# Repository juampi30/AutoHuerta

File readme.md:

# 🌱 AutoHuerta – Sistema Automatizado de Hidroponía Indoor

**AutoHuerta** es un sistema de cultivo hidropónico de interior (*indoor*) diseñado para germinar y desarrollar plantas sin necesidad de suelo agrícola ni luz solar directa. El equipo automatiza los ciclos de iluminación, ventilación y recirculación de nutrientes mediante un microcontrolador **STM32**, permitiendo el cultivo doméstico limpio y autónomo durante todo el año.

Desarrollado por el grupo **HidroTec** (Juan Pablo de Urquiza y Gianluca Mariotto) para la materia *Proyecto y Diseño Electrónico* — E.E.S.T. N° 5 "2 de Abril", Temperley.

---

## ⚙️ Características Principales

* **Iluminación Full Spectrum:** Módulo LED COB Full Spectrum de 50 W (rango PAR 400–700 nm) con fotoperíodo automático de **18 h de luz / 6 h de oscuridad**.
* **Recirculación y Oxigenación Hídrica:** Bomba sumergible de 5 VCC activada **5 minutos por hora** para mantener oxigenada la solución nutritiva y evitar el estancamiento.
* **Control Térmico Sincronizado:** Disipador de aluminio con ventilador axial de 12 VCC accionado junto con la luminaria COB (con soporte para control de velocidad por PWM).
* **Electrónica Protegida y Escalable:** PCB doble faz con etapas de potencia optoacopladas (`PC817`), reguladores independientes (`L7805`) para lógica y motor, y pinera de expansión de 10 pines (7 GPIO + GND + 5 V + 12 V) para futuros sensores o conectividad IoT.

---

## 📂 Estructura del Repositorio

El proyecto está organizado en las siguientes carpetas para facilitar su reproducción:

```text
AutoHuerta/
├── Diseño 3D/      # Planos y modelos 3D del gabinete, soportes de disipador y canastas hidropónicas
├── Hardware/       # Proyecto en KiCad (esquemáticos, diseño de PCB doble faz, render 3D y lista de componentes)
├── Software/       # Código fuente en C/C++ (.ino) para el microcontrolador STM32F103C8T6
└── README.md       # Documentación general del proyecto
```

---

## 🛠️ Requisitos de Hardware y Software

* **Microcontrolador:** STM32F103C8T6 (*Blue Pill*, ARM Cortex-M3).
* **Programador:** ST-Link V2.
* **Entorno de desarrollo:** Arduino IDE con el núcleo **STM32duino** instalado.
* **CAD Electrónico:** KiCad (para abrir los archivos de la carpeta `/Hardware`).

---

## 🚀 Puesta en Marcha Rápida

1. **Preparar la solución nutritiva:** Llenar el recipiente del cajón frontal con agua limpia y agregar dos tapas de nutrientes *macro* y dos tapas de nutrientes *micro*.
2. **Colocar los cultivos:** Ubicar las plántulas en las canastas perforadas asegurando que sus raíces queden en contacto con el agua.
3. **Encender:** Conectar el equipo a la red eléctrica de **220 VCA**. El sistema iniciará automáticamente los ciclos de luz, ventilación y bombeo sin requerir configuración adicional.
4. **Mantenimiento:** Renovar el agua con nutrientes aproximadamente cada **25 días**.

---

## 📄 Licencia y Créditos

Proyecto educativo y de código abierto desarrollado por **HidroTec** — E.E.S.T. N° 5 "2 de Abril" (Temperley, Buenos Aires, Argentina).

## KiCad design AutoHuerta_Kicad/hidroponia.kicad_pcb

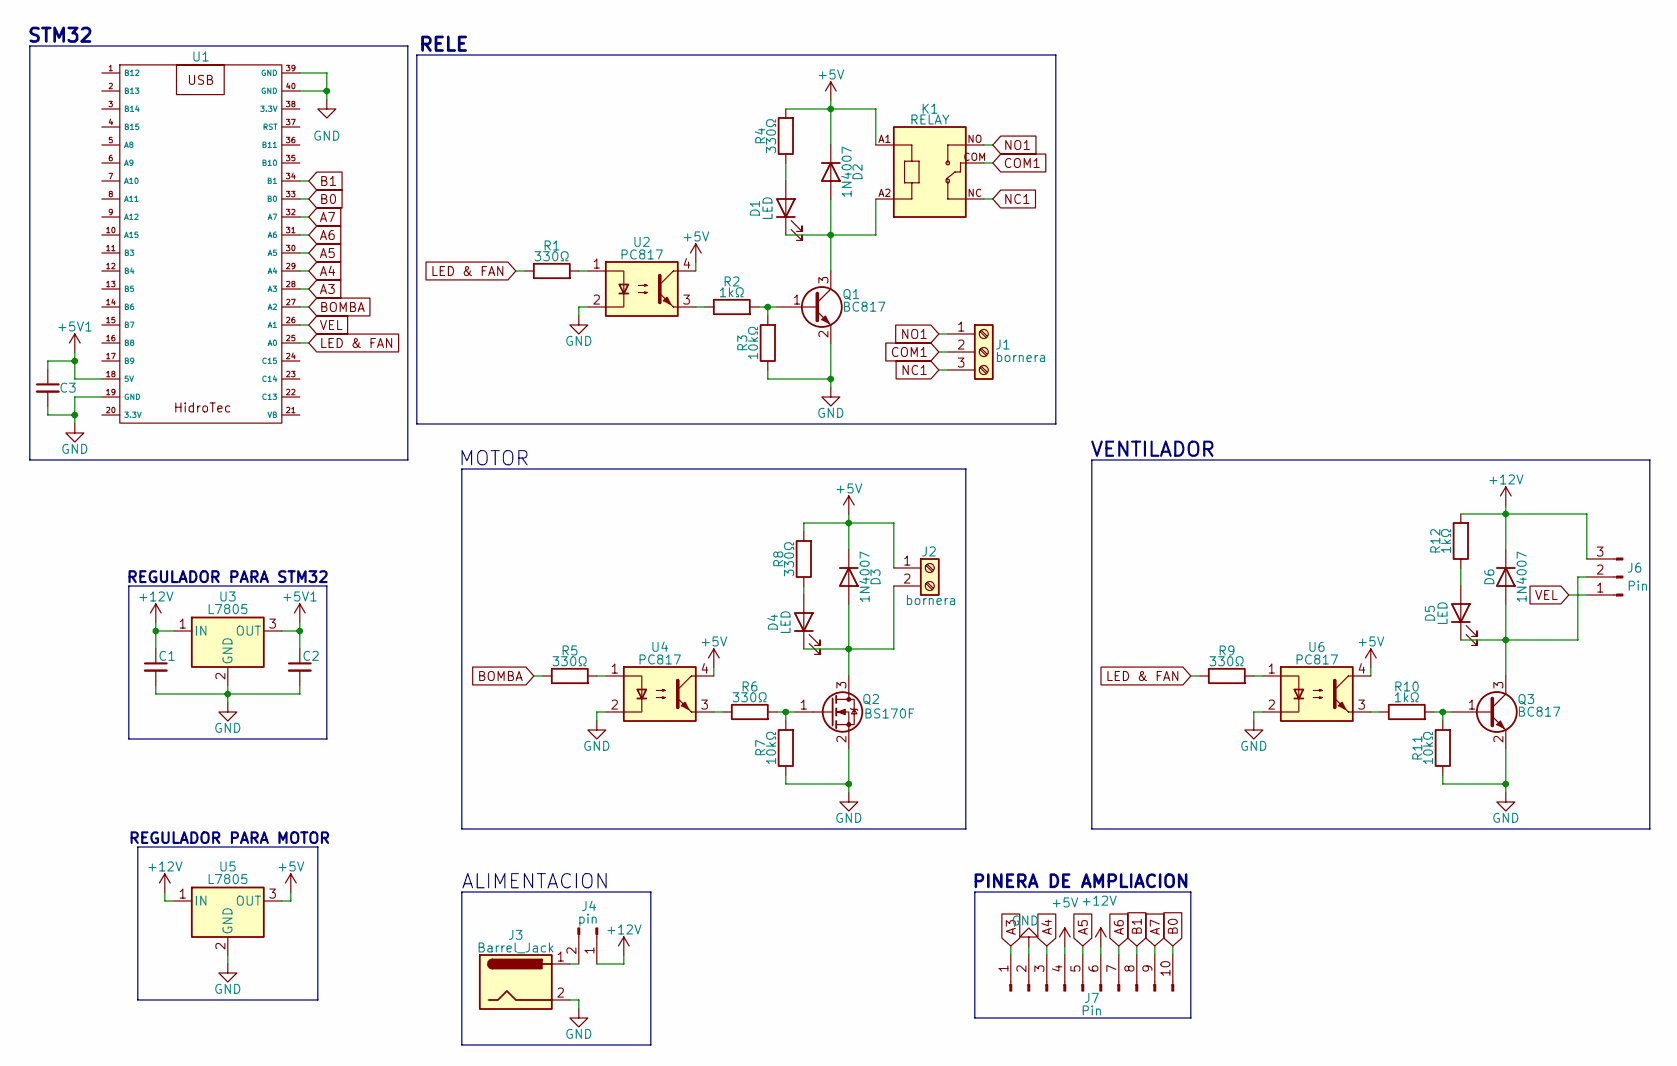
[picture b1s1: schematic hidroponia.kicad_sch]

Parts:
C1: 0,33uf; C_0805_2012Metric_Pad1.18x1.45mm_HandSolder
C2, C3: 0,1uf; C_0805_2012Metric_Pad1.18x1.45mm_HandSolder
D1, D4, D5: LED; LED_D3.0mm
D2, D3, D6: 1N4007; D_SMA
J1: bornera; TerminalBlock_bornier-3_P5.08mm
J2: bornera; TerminalBlock_MetzConnect_Type011_RT05502HBWC_1x02_P5.00mm_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
J3: Barrel_Jack; BarrelJack_GCT_DCJ200-10-A_Horizontal
J4: pin; PinHeader_1x02_P2.54mm_Vertical
J6: Pin; Molex_KK-254_AE-6410-03A_1x03_P2.54mm_Vertical
J7: Pin; IDC-Header_2x05-1MP_P2.54mm_Latch6.5mm_Vertical
K1: RELAY; RELAY_SRD-05VDC-SL-C
Q1, Q3: BC817; SOT-23
Q2: BS170F; SOT-23
R1, R4, R5, R6, R8, R9: 330Ω; R_0805_2012Metric
R2, R10, R12: 1kΩ; R_0805_2012Metric
R3, R7, R11: 10kΩ; R_0805_2012Metric
U1: stm32
U2, U4, U6: PC817; DIP-4_W7.62mm_LongPads
U3, U5: L7805; TO-252-2

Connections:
+5V: D2.1 (K), D3.1 (K), J2.1, J7.4, K1.A1, R4.2, R8.2, U2.4, U4.4, U5.3 (OUT), U6.4
+5V1: C2.1, C3.1, U1.18 (5V), U3.3 (OUT)
+12V: C1.1, D6.1 (K), J4.1, J6.3, J7.6, R12.2, U3.1 (IN), U5.1 (IN)
A3: J7.1, U1.28 (A3)
A4: J7.3, U1.29 (A4)
A5: J7.5, U1.30 (A5)
A6: J7.7, U1.31 (A6)
A7: J7.9, U1.32 (A7)
B0: J7.10, U1.33 (B0)
B1: J7.8, U1.34 (B1)
BOMBA: R5.1, U1.27 (A2)
COM1: J1.2, K1.COM
GND: C1.2, C2.2, C3.2, J3.2, J7.2, Q1.2 (E), Q2.2 (S), Q3.2 (E), R3.1, R7.1, R11.1, U1.19 (GND), U1.39 (GND), U1.40 (GND), U2.2, U3.2 (GND), U4.2, U5.2 (GND), U6.2
LED & FAN: R1.1, R9.1, U1.25 (A0)
NC1: J1.3, K1.NC
NO1: J1.1, K1.NO
unnamed: D1.2 (A), R4.1
unnamed: D1.1 (K), D2.2 (A), K1.A2, Q1.3 (C)
unnamed: D3.2 (A), D4.1 (K), J2.2, Q2.3 (D)
unnamed: D4.2 (A), R8.1
unnamed: D5.2 (A), R12.1
unnamed: D5.1 (K), D6.2 (A), J6.2, Q3.3 (C)
unnamed: J3.1, J4.2
unnamed: Q1.1 (B), R2.2, R3.2
unnamed: Q2.1 (G), R6.2, R7.2
unnamed: Q3.1 (B), R10.2, R11.2
unnamed: R1.2, U2.1
unnamed: R2.1, U2.3
unnamed: R5.2, U4.1
unnamed: R6.1, U4.3
unnamed: R9.2, U6.1
unnamed: R10.1, U6.3
VEL: J6.1, U1.26 (A1)

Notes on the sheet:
RELE
REGULADOR PARA STM32
STM32
REGULADOR PARA MOTOR
ALIMENTACION
VENTILADOR
PINERA DE AMPLIACION
MOTOR

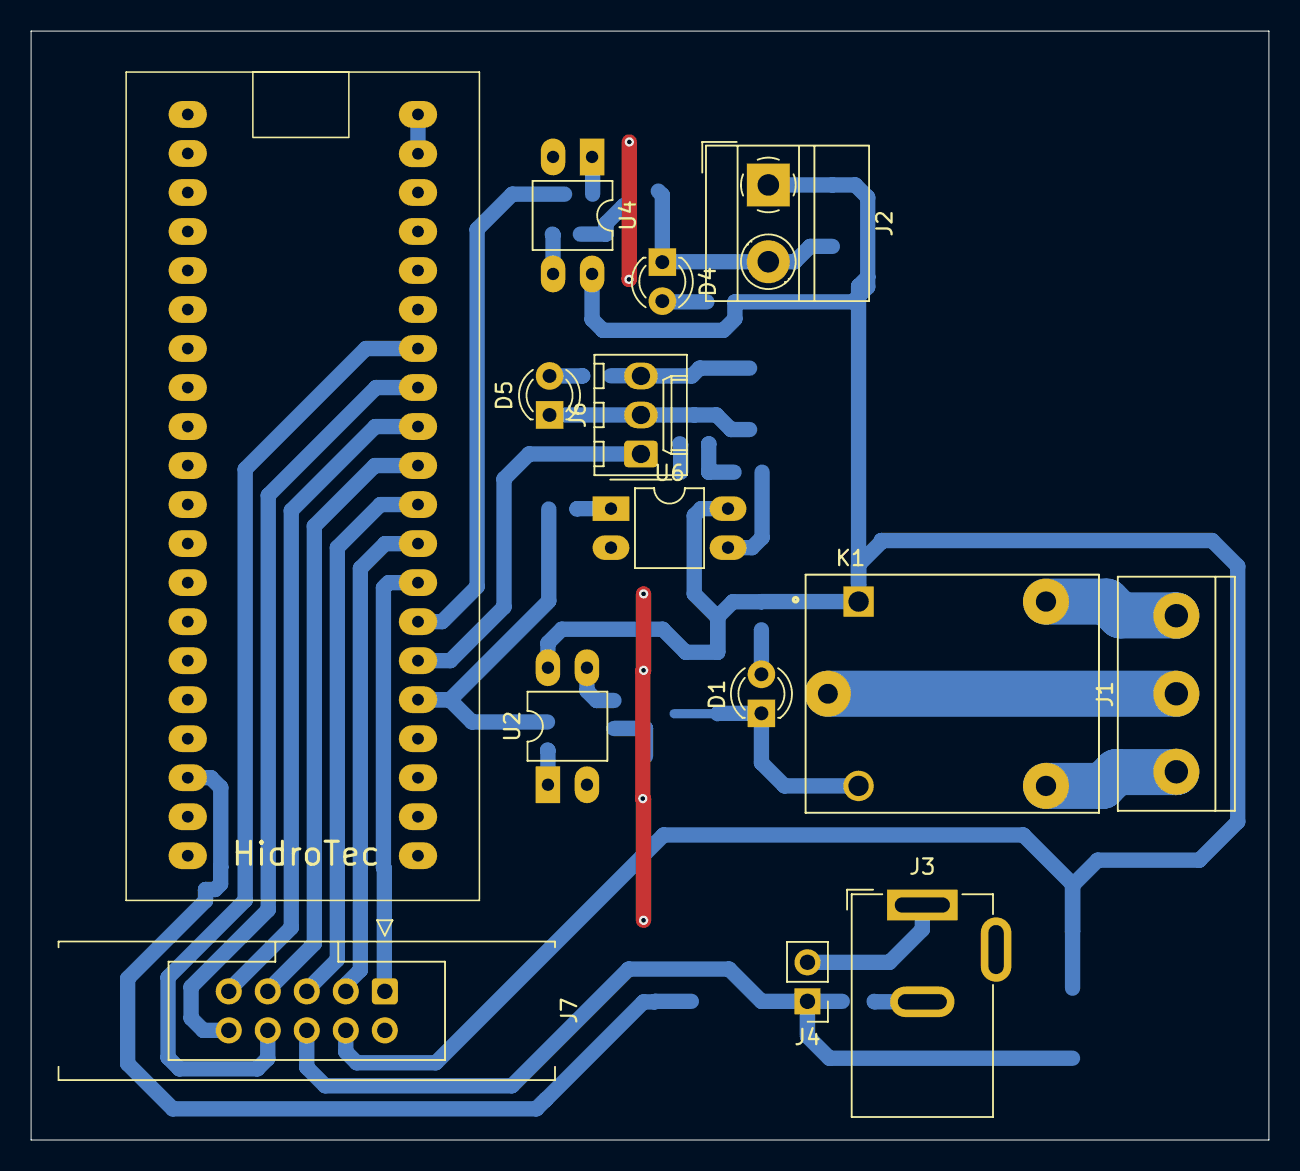
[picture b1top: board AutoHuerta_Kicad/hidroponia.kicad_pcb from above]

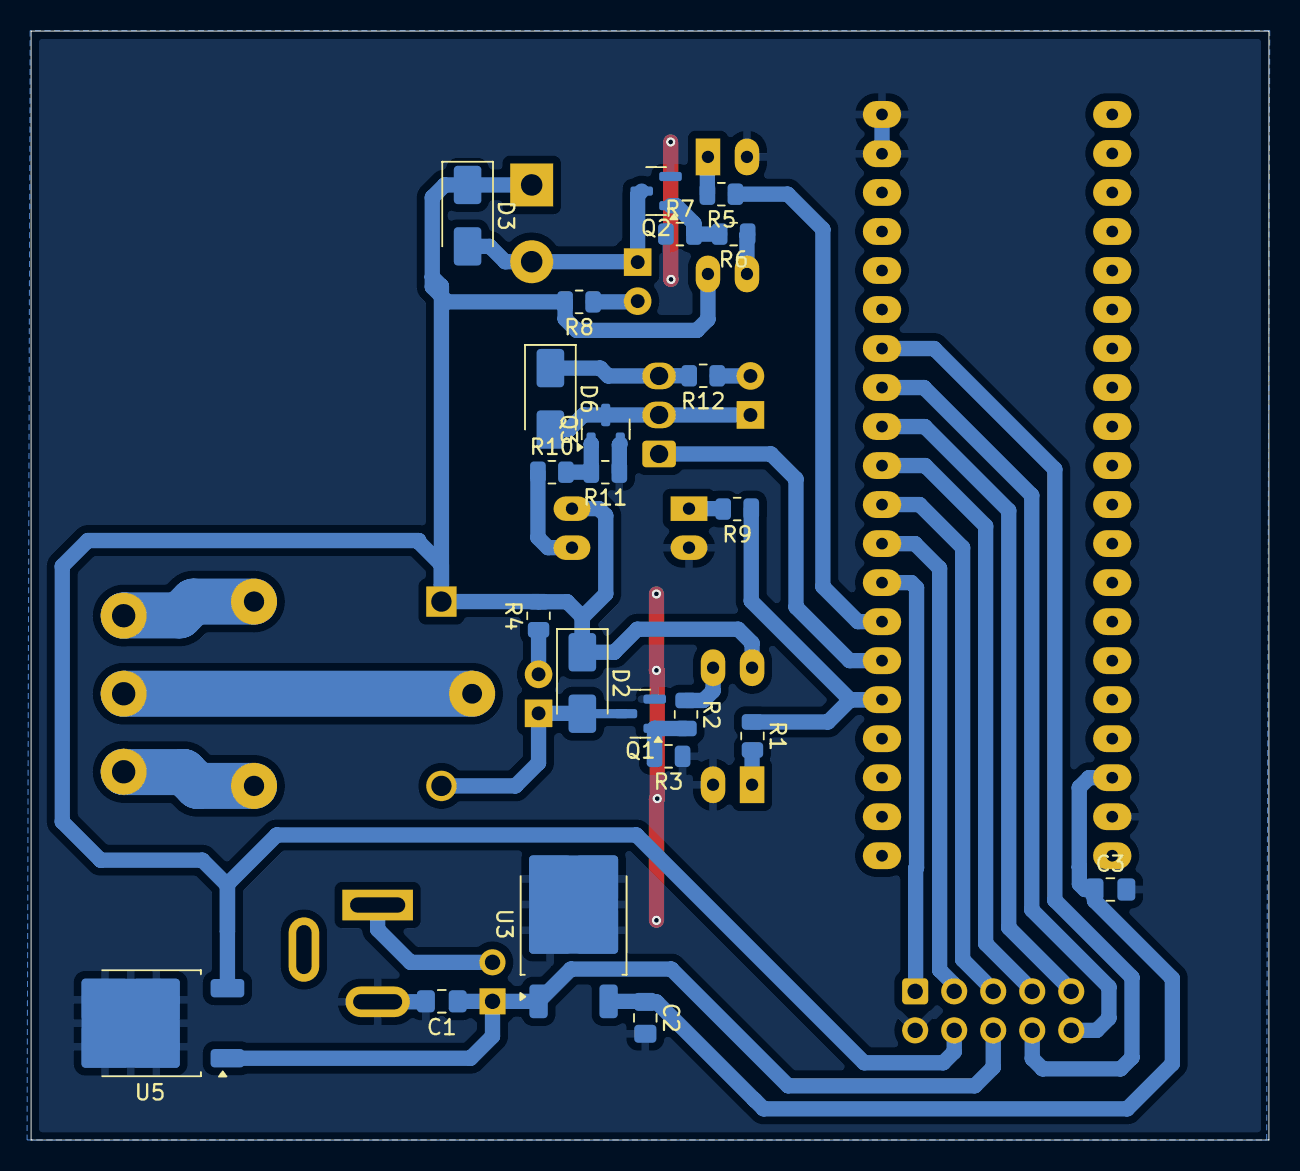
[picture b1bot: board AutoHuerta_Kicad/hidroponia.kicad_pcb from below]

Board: 2 copper layers, 80.6 x 72.2 mm, 37 parts (23 on the bottom side), 33 nets.

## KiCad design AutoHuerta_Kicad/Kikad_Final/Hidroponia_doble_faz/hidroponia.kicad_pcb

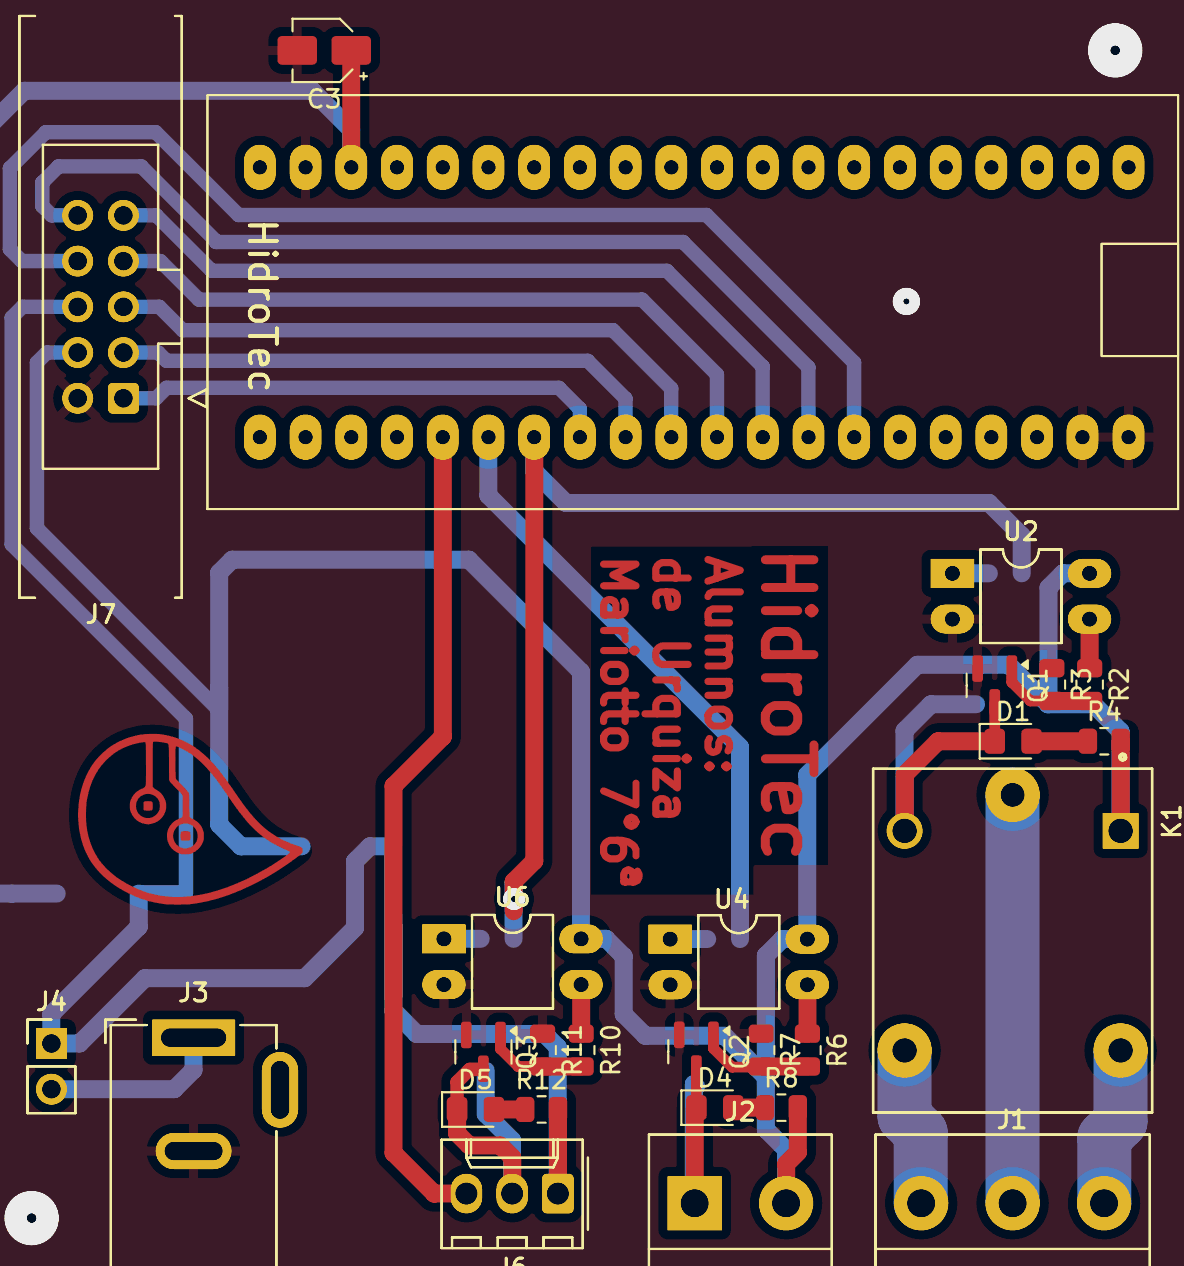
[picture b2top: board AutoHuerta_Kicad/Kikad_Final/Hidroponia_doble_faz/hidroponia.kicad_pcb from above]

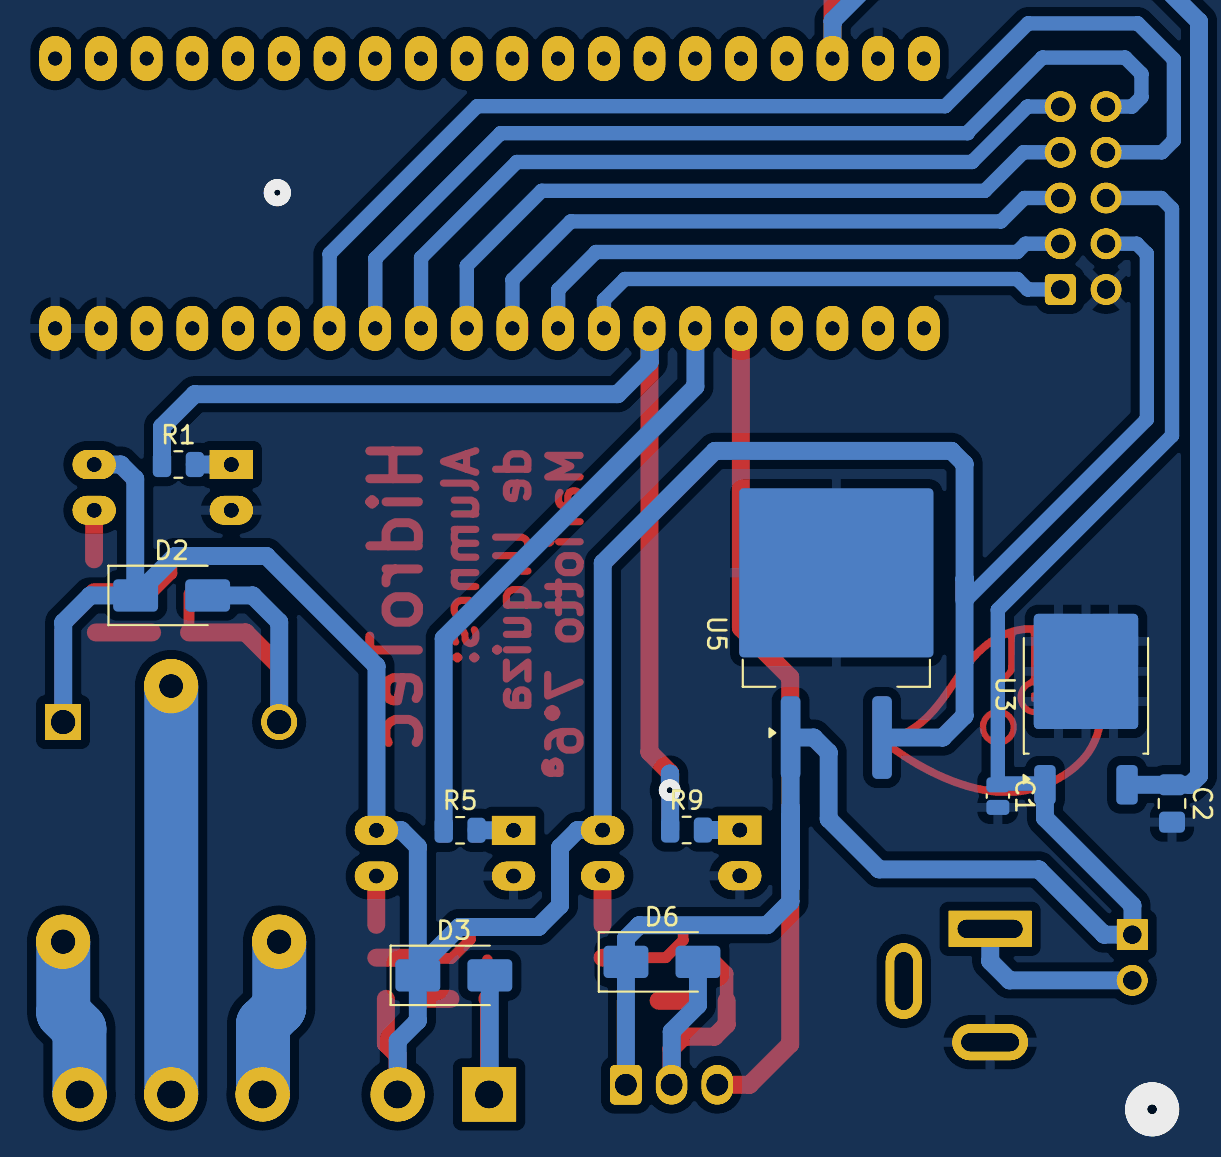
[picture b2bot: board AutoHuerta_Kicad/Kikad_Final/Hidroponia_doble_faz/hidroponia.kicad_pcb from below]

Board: 2 copper layers, 48 parts (10 on the bottom side), 33 nets.

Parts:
C1: 0,33uf; C_0504_1310Metric_Pad0.83x1.28mm_HandSolder
C2: 0,1uf; C_0805_2012Metric_Pad1.18x1.45mm_HandSolder
C3: 0,1uf; CP_Elec_3x5.4
D1, D4, D5: LED; LED_0805_2012Metric_Pad1.15x1.40mm_HandSolder
D2, D3, D6: 1N4007; D_SMA
J1, J1#2: bornera; TerminalBlock_bornier-3_P5.08mm
J2, J2#2: bornera; TerminalBlock_bornier-2_P5.08mm
J3, J3#2: Barrel_Jack; BarrelJack_GCT_DCJ200-10-A_Horizontal
J4, J4#2: pin; PinHeader_1x02_P2.54mm_Vertical
J6, J6#2: Pin; Molex_KK-254_AE-6410-03A_1x03_P2.54mm_Vertical
J7, J7#2: Pin; IDC-Header_2x05-1MP_P2.54mm_Latch6.5mm_Vertical
K1, K1#2: RELAY; RELAY_SRD-05VDC-SL-C
Q1, Q3: BC817; SOT-23
Q2: BS170F; SOT-23
R1, R4, R5, R6, R8, R9: 330Ω; R_0805_2012Metric
R2, R10, R12: 1kΩ; R_0805_2012Metric
R3, R7, R11: 10kΩ; R_0805_2012Metric
U1, U1#2: stm32
U2, U2#2, U4, U4#2, U6, U6#2: PC817; DIP-4_W7.62mm_LongPads
U3: L7805; TO-252-2
U5: L7805; TO-263-2_TabPin1

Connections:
+5V: D2.1 (K), D3.1 (K), J2.2, J2#2.2, J7.4, J7#2.4, K1.A1, K1#2.A1, R4.2, R8.2, U2.4, U2#2.4, U4.4, U4#2.4, U5.2 (GND), U6.4, U6#2.4
+5V1: C2.1, C3.1, U1.18 (5V), U1#2.18 (5V), U3.3 (OUT)
+12V: C1.1, D6.1 (K), J4.1, J4#2.1, J6.1, J6#2.1, J7.6, J7#2.6, R12.2, U3.1 (IN), U5.1 (IN)
A3: J7.1, J7#2.1, U1.28 (A3), U1#2.28 (A3)
A4: J7.3, J7#2.3, U1.29 (A4), U1#2.29 (A4)
A5: J7.5, J7#2.5, U1.30 (A5), U1#2.30 (A5)
A6: J7.7, J7#2.7, U1.31 (A6), U1#2.31 (A6)
A7: J7.9, J7#2.9, U1.32 (A7), U1#2.32 (A7)
B0: J7.10, J7#2.10, U1.33 (B0), U1#2.33 (B0)
B1: J7.8, J7#2.8, U1.34 (B1), U1#2.34 (B1)
BOMBA: R5.1, U1.26 (A1), U1#2.26 (A1)
COM1: J1.2, J1#2.2, K1.COM, K1#2.COM
GND: C1.2, C2.2, C3.2, J3.2, J3#2.2, J7.2, J7#2.2, Q1.2 (E), Q2.2 (S), Q3.2 (E), R3.1, R7.1, R11.1, U1.19 (GND), U1.39 (GND), U1.40 (GND), U1#2.19 (GND), U1#2.39 (GND), U1#2.40 (GND), U2.2, U2#2.2, U3.2 (GND), U4.2, U4#2.2, U5.1 (IN), U6.2, U6#2.2
LED & FAN: R1.1, R9.1, U1.27 (A2), U1#2.27 (A2)
NC1: J1.3, J1#2.3, K1.NC, K1#2.NC
NO1: J1.1, J1#2.1, K1.NO, K1#2.NO
unnamed: D1.2 (A), R4.1
unnamed: D1.1 (K), D2.2 (A), K1.A2, K1#2.A2, Q1.3 (C)
unnamed: D3.2 (A), D4.1 (K), J2.1, J2#2.1, Q2.3 (D)
unnamed: D4.2 (A), R8.1
unnamed: D5.2 (A), R12.1
unnamed: D5.1 (K), D6.2 (A), J6.2, J6#2.2, Q3.3 (C)
unnamed: J3.1, J3#2.1, J4.2, J4#2.2
unnamed: Q1.1 (B), R2.2, R3.2
unnamed: Q2.1 (G), R6.2, R7.2
unnamed: Q3.1 (B), R10.2, R11.2
unnamed: R1.2, U2.1, U2#2.1
unnamed: R2.1, U2.3, U2#2.3
unnamed: R5.2, U4.1, U4#2.1
unnamed: R6.1, U4.3, U4#2.3
unnamed: R9.2, U6.1, U6#2.1
unnamed: R10.1, U6.3, U6#2.3
VEL: J6.3, J6#2.3, U1.25 (A0), U1#2.25 (A0)

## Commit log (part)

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2026-04-08 Create AutoHueta.gan
    Diagrama de Gantt
2026-04-15 AutoHuerta
    Añadi la carpeta AutoHuerta de kicad
2026-04-15 Agregue carpetas
    Ideas de logos para HidroTec
2026-04-15 Actualizacion de placa
    agregamos la entrada de 12v, agregamos el control para el motor, tambien pusimos huellas.
2026-04-17 Actualizacion de plaqueta 17/4
    agregue el control del ventilador, agregue capacito para stm32, puse huellas faltantes y conecte los pines del stm32
2026-04-22 Actualizacion de placa
    Agregamos pinera de 8 pines y tambien agregamos control de velocidad para el ventilador.
2026-04-22 Añadí el Logo
    Ordene carpetas y puse el logo en simbolo y huella
2026-04-22 Esquematico terminado
    Terminamos de corregir y agregar cosas al esquematico y empezamos a acomodar los componentes en el pcb
2026-04-24 PCB
    Acomodamos un poco el PCB y cambiamos pines de lugar
2026-04-29 PCB
    PCB casi terminado, y cambiamos unas cosas del esquematico
2026-05-06 commit d vuelta
2026-05-06 prueba fin
    quilombo areglado
2026-05-06 PCB
    cambios en el pcb
2026-05-17 PCB actualizado
    faltan enrutar 5 pistas
2026-05-20 actualizacion de PCB
    pruebas
2026-06-03 pcb doble faz casi listo
    pcb casi terminado
2026-06-05 PCB TERMINADO
    Terminamos el PCB
2026-06-16 gantt actualizado
